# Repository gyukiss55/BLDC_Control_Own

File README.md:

# BLDC_Control_Own
BLDC

- 1.00.00 Add sources
- 1.01.00 ESC A,B,C uart control tested
- 1.02.00 Win32UARTControl added
- 1.03.00 STM32F103_3_PWM_Test, STM32F4xx_3_PWM_Test added

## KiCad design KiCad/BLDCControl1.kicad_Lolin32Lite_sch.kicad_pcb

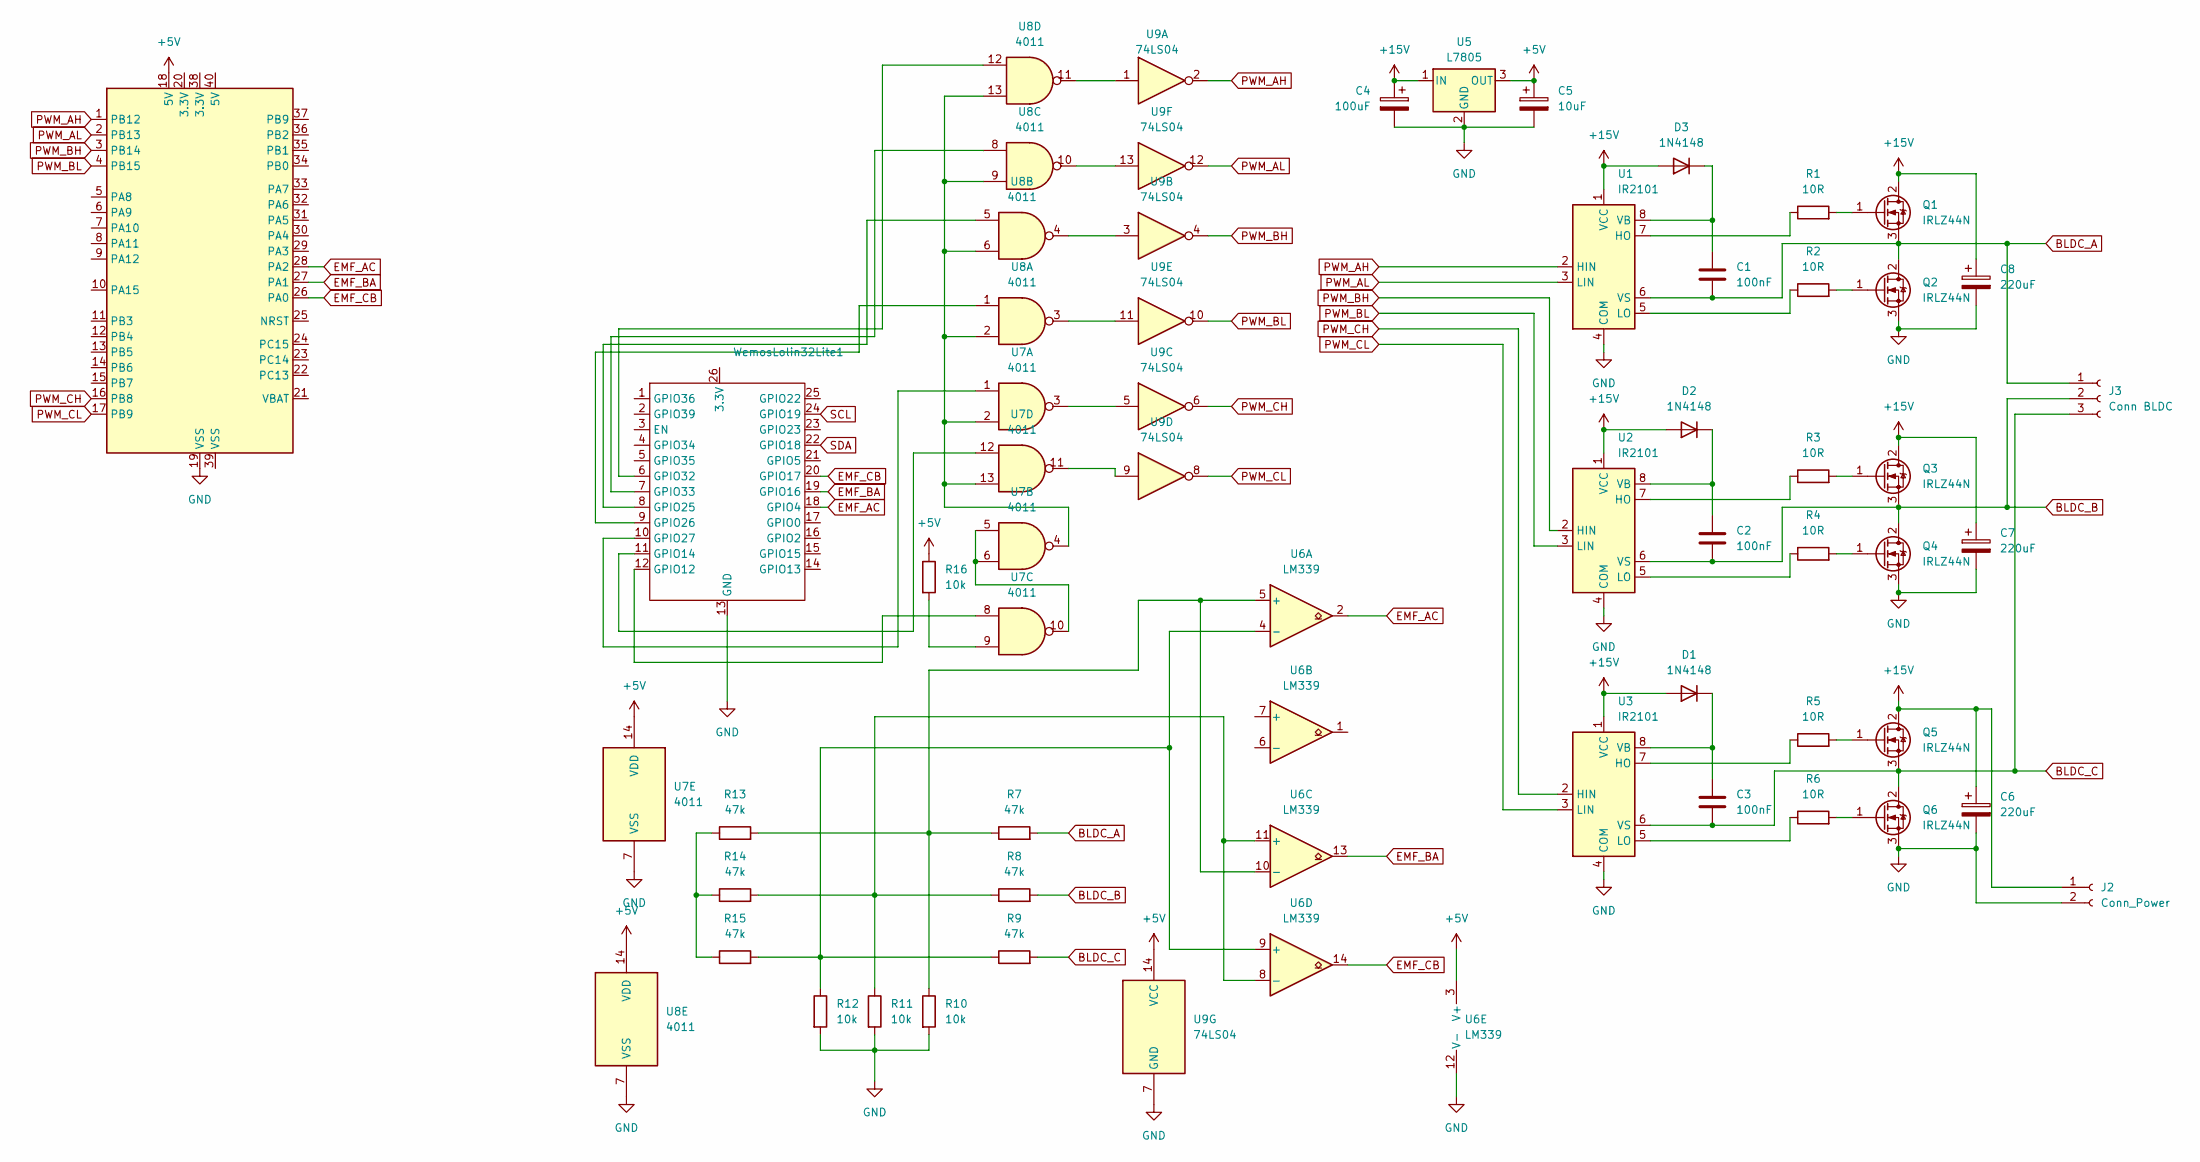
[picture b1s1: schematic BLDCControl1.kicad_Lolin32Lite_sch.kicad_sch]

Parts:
C1, C2, C3: 100nF; C_Axial_L3.8mm_D2.6mm_P7.50mm_Horizontal
C4: 100uF; CP_Radial_D6.3mm_P2.50mm
C5: 10uF; CP_Radial_D6.3mm_P2.50mm
C6, C7, C8: 220uF; CP_Radial_D6.3mm_P2.50mm
D1, D2, D3: 1N4148; D_DO-35_SOD27_P7.62mm_Horizontal
J2: Conn_Power; PinHeader_1x02_P2.54mm_Vertical
J3: Conn BLDC; PinSocket_1x03_P2.54mm_Vertical
Q1, Q2, Q3, Q4, Q5, Q6: IRLZ44N; TO-220-3_Vertical
R1, R2, R3, R4, R5, R6: 10R; R_Axial_DIN0204_L3.6mm_D1.6mm_P5.08mm_Horizontal
R7, R8, R9, R13, R14, R15: 47k; R_Axial_DIN0204_L3.6mm_D1.6mm_P5.08mm_Horizontal
R10, R11, R12, R16: 10k; R_Axial_DIN0204_L3.6mm_D1.6mm_P5.08mm_Horizontal
U1, U2, U3: IR2101; DIP-8_W7.62mm
U5: L7805; TO-220-3_Vertical
U6: LM339; DIP-14_W7.62mm
U7, U8: 4011; CERDIP-14_W7.62mm_SideBrazed
U9: 74LS04; CERDIP-14_W7.62mm_SideBrazed
U10: STM32F411CE_BlackPill; DIP-40_W15.24mm
WemosLolin32Lite1: DIP-26_900_WEMOS_LOLIN32_LITE

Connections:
+5V: C5.1, R16.1, U5.3 (OUT), U6.3 (V+), U7.14 (VDD), U8.14 (VDD), U9.14 (VCC), U10.18 (5V)
+15V: C4.1, C6.1, C7.1, C8.1, D1.2 (A), D2.2 (A), D3.2 (A), J2.1, Q1.2 (D), Q3.2 (D), Q5.2 (D), U1.1 (VCC), U2.1 (VCC), U3.1 (VCC), U5.1 (IN)
BLDC_A: C1.2, J3.1, Q1.3 (S), Q2.2 (D), R7.2, U1.6 (VS)
BLDC_B: C2.2, J3.2, Q3.3 (S), Q4.2 (D), R8.2, U2.6 (VS)
BLDC_C: C3.2, J3.3, Q5.3 (S), Q6.2 (D), R9.2, U3.6 (VS)
EMF_AC: U6.2, U10.28 (PA2), WemosLolin32Lite1.18 (GPIO4)
EMF_BA: U6.13, U10.27 (PA1), WemosLolin32Lite1.19 (GPIO16)
EMF_CB: U6.14, U10.26 (PA0), WemosLolin32Lite1.20 (GPIO17)
GND: C4.2, C5.2, C6.2, C7.2, C8.2, J2.2, Q2.3 (S), Q4.3 (S), Q6.3 (S), R10.2, R11.2, R12.2, U1.4 (COM), U2.4 (COM), U3.4 (COM), U5.2 (GND), U6.12 (V-), U7.7 (VSS), U8.7 (VSS), U9.7 (GND), U10.19 (VSS), U10.35 (VSS), U10.47 (VSS), U10.49 (VSS), WemosLolin32Lite1.13 (GND)
unnamed: C3.1, D1.1 (K), U3.8 (VB)
unnamed: C2.1, D2.1 (K), U2.8 (VB)
unnamed: C1.1, D3.1 (K), U1.8 (VB)
unnamed: Q1.1 (G), R1.2
unnamed: Q2.1 (G), R2.2
unnamed: Q3.1 (G), R3.2
unnamed: Q4.1 (G), R4.2
unnamed: Q5.1 (G), R5.2
unnamed: Q6.1 (G), R6.2
unnamed: R13.1, R14.1, R15.1
unnamed: R16.2, U7.9
unnamed: R1.1, U1.7 (HO)
unnamed: R2.1, U1.5 (LO)
unnamed: R3.1, U2.7 (HO)
unnamed: R4.1, U2.5 (LO)
unnamed: R5.1, U3.7 (HO)
unnamed: R6.1, U3.5 (LO)
unnamed: R7.1, R10.1, R13.2, U6.5 (+), U6.10 (-)
unnamed: R9.1, R12.1, R15.2, U6.4 (-), U6.9 (+)
unnamed: R8.1, R11.1, R14.2, U6.8 (-), U6.11 (+)
unnamed: U7.3, U9.5
unnamed: U7.5, U7.6, U7.10
unnamed: U7.11, U9.9
unnamed: U7.2, U7.4, U7.13, U8.2, U8.6, U8.9, U8.13
unnamed: U8.3, U9.11
unnamed: U8.4, U9.3
unnamed: U8.10, U9.13
unnamed: U8.11, U9.1
unnamed: U7.8, WemosLolin32Lite1.12 (GPIO12)
unnamed: U7.12, WemosLolin32Lite1.11 (GPIO14)
unnamed: U8.5, WemosLolin32Lite1.8 (GPIO25)
unnamed: U8.1, WemosLolin32Lite1.9 (GPIO26)
unnamed: U7.1, WemosLolin32Lite1.10 (GPIO27)
unnamed: U8.12, WemosLolin32Lite1.6 (GPIO32)
unnamed: U8.8, WemosLolin32Lite1.7 (GPIO33)
PWM_AH: U1.2 (HIN), U9.2, U10.1 (PB12)
PWM_AL: U1.3 (LIN), U9.12, U10.2 (PB13)
PWM_BH: U2.2 (HIN), U9.4, U10.3 (PB14)
PWM_BL: U2.3 (LIN), U9.10, U10.4 (PB15)
PWM_CH: U3.2 (HIN), U9.6, U10.16 (PB8)
PWM_CL: U3.3 (LIN), U9.8, U10.17 (PB9)
SCL: WemosLolin32Lite1.24 (GPIO19)
SDA: WemosLolin32Lite1.22 (GPIO18)

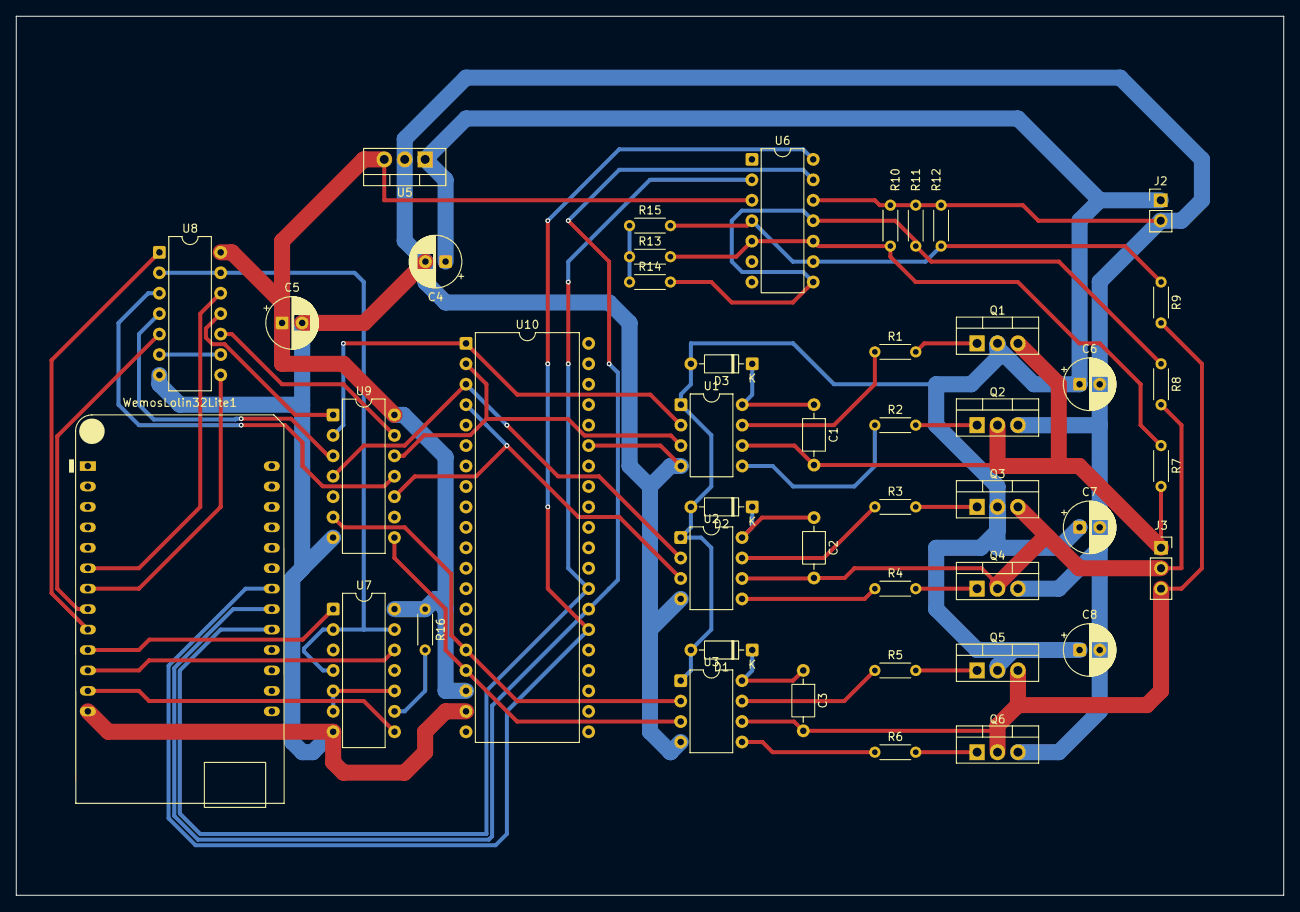
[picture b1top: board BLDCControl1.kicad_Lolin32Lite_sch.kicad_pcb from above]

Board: 2 copper layers, 157.5 x 109.2 mm, 45 parts (0 on the bottom side), 50 nets.

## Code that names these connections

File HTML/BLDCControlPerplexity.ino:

// Perplexity
// Black Pill STM32F411CE BLDC Control Project
// Select board: Generic F411CE in Arduino IDE with STM32 core

// Volatile global parameters
volatile int vol_m_control = 0;  // 0-Stop, 1-Async, 2-Listening, 3-Sync
volatile int vol_ti_ix = 0;      // Timer index
volatile uint32_t vol_ti_ts[32] = {0};  // Timer timestamps
volatile uint8_t vol_ti_BLDC[32] = {0}; // BLDC states (note: byte array)
volatile int vol_ei_ix = 0;      // External interrupt index
volatile uint32_t vol_ei_ts[32] = {0};  // EI timestamps micros
volatile int vol_ei_inp[32] = {0};     // EI inputs PA0,PA1,PA2 status

// BLDC pins: PB12,13,14,15,8,9 -> bits 12,13,14,15,8,9 in GPIOB->ODR
#define BLDC_MASK  ((1<<12)|(1<<13)|(1<<14)|(1<<15)|(1<<8)|(1<<9))

HardwareTimer *MyTim = NULL;

void TimerHandler(void) {
  uint32_t ts = micros();
  vol_ti_ts[vol_ti_ix] = ts;
  // Apply BLDC state - direct port access [web:21]
  GPIOB->ODR = (GPIOB->ODR & ~BLDC_MASK) | (vol_ti_BLDC[vol_ti_ix] & BLDC_MASK);
  vol_ti_ix = (vol_ti_ix + 1) % 32;
}

void ExtInterruptHandler() {
  uint32_t ts = micros();
  uint16_t inp = GPIOA->IDR & 0x07;  // PA0,PA1,PA2 bits 0,1,2
  vol_ei_ts[vol_ei_ix] = ts;
  vol_ei_inp[vol_ei_ix] = inp;
  vol_ei_ix = (vol_ei_ix + 1) % 32;
}

void setup() {
  // BLDC outputs PB12-PB15,PB8,PB9 [web:1]
  pinMode(PB12, OUTPUT);
  pinMode(PB13, OUTPUT);
  pinMode(PB14, OUTPUT);
  pinMode(PB15, OUTPUT);
  pinMode(PB8, OUTPUT);
  pinMode(PB9, OUTPUT);

  // External interrupts PA0,PA1,PA2 both directions (CHANGE) [web:20]
  pinMode(PA0, INPUT);
  pinMode(PA1, INPUT);
  pinMode(PA2, INPUT);
  attachInterrupt(PA0, ExtInterruptHandler, CHANGE);
  attachInterrupt(PA1, ExtInterruptHandler, CHANGE);
  attachInterrupt(PA2, ExtInterruptHandler, CHANGE);

  // Timer interrupt 10us period [web:16][web:13]
  // STM32F411 100MHz sysclk, timer x2 -> 200MHz, prescaler=1 (0), period=1999 (~10us)
  MyTim = new HardwareTimer(TIM2);
  MyTim->setOverflow(1999, TICK_FORMAT);  // 200MHz / 2000 = 100kHz = 10us
  MyTim->attachInterrupt(TimerHandler);
  MyTim->resume();

  Serial.begin(115200);
}

void loop() {
  // Example: set mode via serial or leave as is
  if (Serial.available()) {
    int cmd = Serial.parseInt();
    vol_m_control = cmd;
    Serial.print("Mode set to: ");
    Serial.println(vol_m_control);
  }

  // Mode-dependent logic can be added here
  // For now, arrays are filled by interrupts
  delay(100);
}

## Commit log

2024-09-23 Add sources
2024-09-23 Fix EEPROM, PC13
2024-09-23 ESCControl+
2024-09-24 Period and pulse
2024-09-24 uart control tested
2024-09-24 Win32UARTControl
2024-09-24 readme
2024-09-25 kicad project
2024-09-27 fix period and pulse command
2024-09-27 ppn function
2024-09-29 cycle number
2024-09-29 one shot
2024-09-29 sample nr
2024-10-17 STM32PWM6ch
2024-10-17 STM32F411PWM6chv3
2024-10-17 STM32F411PWM
2024-10-17 v3 1
2024-10-17 ChatGPT
2024-10-18 sync
2024-10-18 sync2
2024-10-18 sync3 pa0-3 6-7
2024-10-18 stm32 v2
2025-03-23 6 pwm test
2025-03-23 test 2
2025-03-23 test 1 -a9, -a10
2025-03-23 bluepill
2025-03-24 blue fix
2025-03-29 bldc 6 phase
2025-03-29 Serail input handling
2025-04-01 STM32F4xx_3_PWM_Test added
2026-02-18 UART, LED
2026-02-18 PWM 6 Pin
2026-02-18 html control
2026-02-19 KiCad
2026-02-19 Timer IT / Ext IT
2026-02-19 c# WinSerialControl
2026-02-20 BLDCControl
2026-02-20 fix control, unit test
2026-02-22 Digi scope
2026-02-23 remove printf
2026-02-23 RGB test
2026-02-23 BLD Control fix 0.9
2026-02-23 gitignoret
2026-02-23 fix BLDC_Control
2026-02-24 bldc control
2026-02-26 wemos lolin
2026-02-26 wemos pic
2026-02-27 ESP32 DigiScope
2026-02-27 lilo32 BLDC
2026-03-04 i2c fixed
2026-03-04 KiCad update
2026-03-12 switch control
2026-03-19 fix code
2026-03-20 pwm mode
2026-03-24 Piko measure inductivity
2026-03-25 Lolin32 bldc
2026-03-26 Lolin BLDC Control
2026-03-26 fix bldc web
2026-03-27 fix 2
2026-03-27 signal process
2026-03-28 fix pwm
2026-03-28 time
2026-03-30 current measure kicad
2026-03-31 bldc fix
2026-04-01 BLDCPwmControl
2026-04-01 pico pwm
2026-04-02 pico pwm step2
2026-04-02 chat
2026-04-02 pwm no update
2026-04-02 Revert "pwm no update"
    This reverts commit c8afe281e1a3f00f58123a8815739f2d8f383c6a.
2026-04-10 PicoDrone
2026-04-10 MPU6500
2026-04-11 PicoDronV1
2026-04-12 PicoDroneV1 fix
2026-04-12 BT , WifiClient.py
2026-04-21 QMC5883
2026-04-21 QMC5883L
2026-05-09 esp32_test
2026-05-10 pico 10 DOF
2026-06-10 new moduls
2026-06-12 PWM + IMU
2026-06-12 stm32 imu fix
2026-06-16 pico test
2026-06-17 update pico gy-91 gyro acc pressure
2026-06-17 pico imu, uart1
2026-06-17 pico imu v1.1
2026-06-17 cosmetica
2026-06-19 gy91 udp
2026-06-19 cosmetic
2026-06-19 pico w server
2026-06-20 personal hotspot
